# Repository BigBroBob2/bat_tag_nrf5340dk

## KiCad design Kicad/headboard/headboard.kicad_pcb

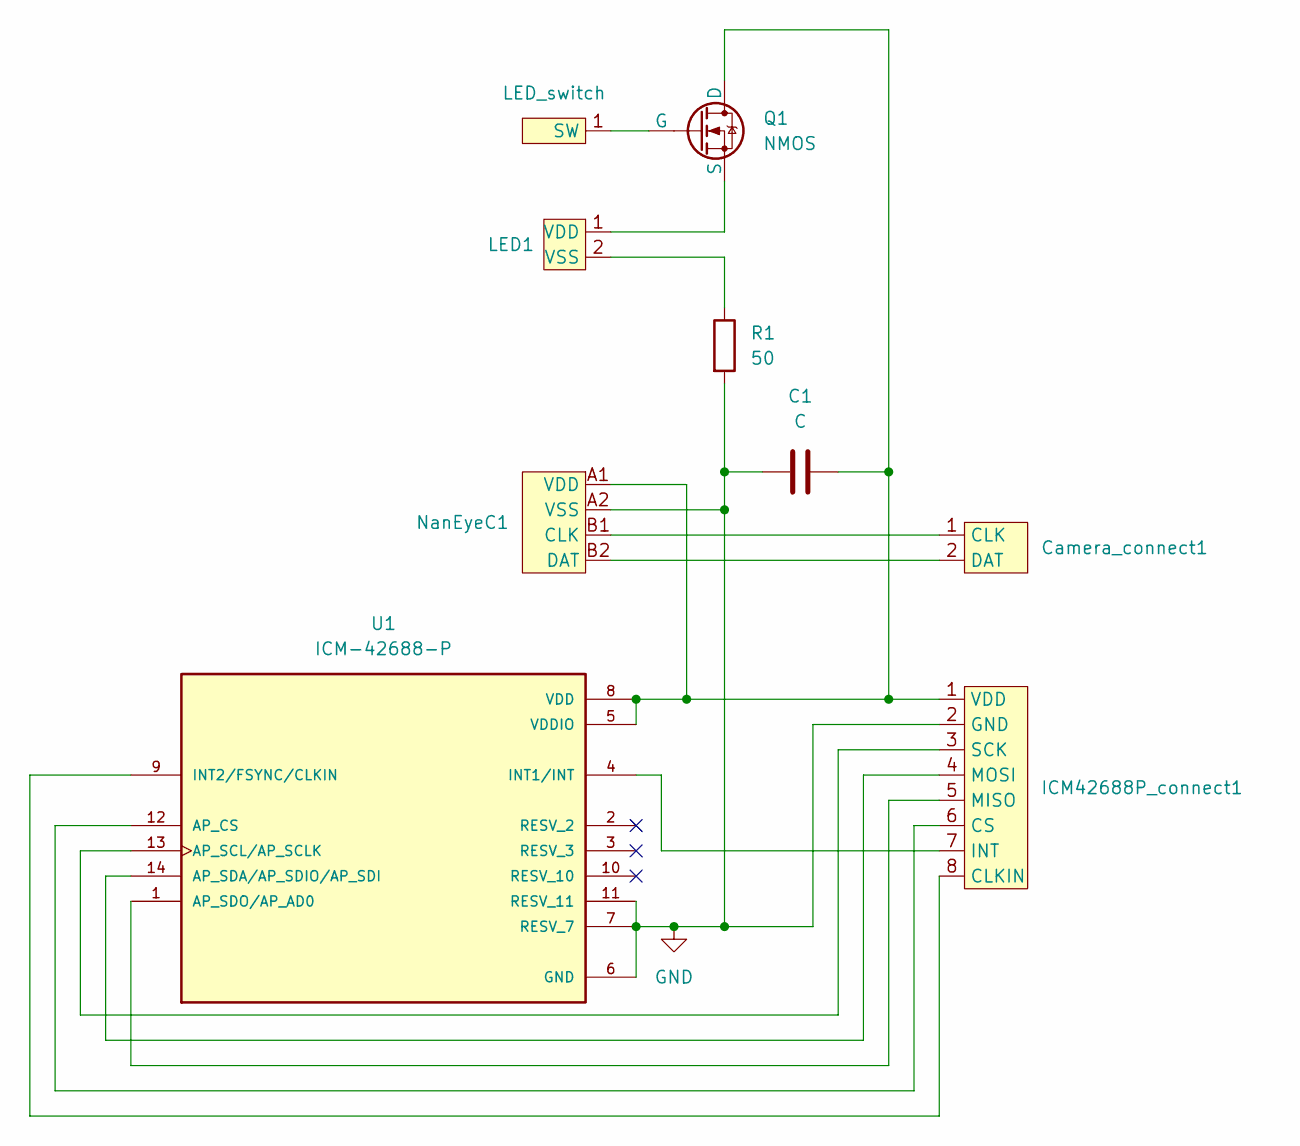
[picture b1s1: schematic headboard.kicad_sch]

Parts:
C1: C; C_0603_1608Metric
Camera_connect1: camera_connect
Camera_connect2: LED_switch
ICM42688P_connect1: ICM42688P_connect
LED1: LED_1206_3216Metric
NanEyeC1: NanEyeC
Q1: NMOS; SOT-23
R1: 50; R_0603_1608Metric
U1: ICM-42688-P; PQFN50P300X250X97-14N; PARTREV 1.2

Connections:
GND: C1.1, ICM42688P_connect1.2 (GND), NanEyeC1.A2 (VSS), R1.2, U1.6 (GND), U1.7 (RESV_7), U1.11 (RESV_11)
unnamed: Camera_connect1.1 (CLK), NanEyeC1.B1 (CLK)
unnamed: Camera_connect1.2 (DAT), NanEyeC1.B2 (DAT)
unnamed: Camera_connect2.1 (SW), Q1.2 (G)
unnamed: ICM42688P_connect1.8 (CLKIN), U1.9 (INT2/FSYNC/CLKIN)
unnamed: ICM42688P_connect1.6 (CS), U1.12 (AP_CS)
unnamed: ICM42688P_connect1.7 (INT), U1.4 (INT1/INT)
unnamed: ICM42688P_connect1.5 (MISO), U1.1 (AP_SDO/AP_AD0)
unnamed: ICM42688P_connect1.4 (MOSI), U1.14 (AP_SDA/AP_SDIO/AP_SDI)
unnamed: ICM42688P_connect1.3 (SCK), U1.13 (AP_SCL/AP_SCLK)
unnamed: C1.2, ICM42688P_connect1.1 (VDD), NanEyeC1.A1 (VDD), Q1.1 (D), U1.5 (VDDIO), U1.8 (VDD)
unnamed: LED1.1 (VDD), Q1.3 (S)
unnamed: LED1.2 (VSS), R1.1

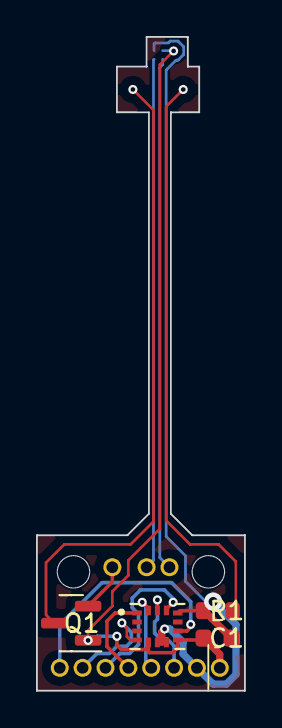
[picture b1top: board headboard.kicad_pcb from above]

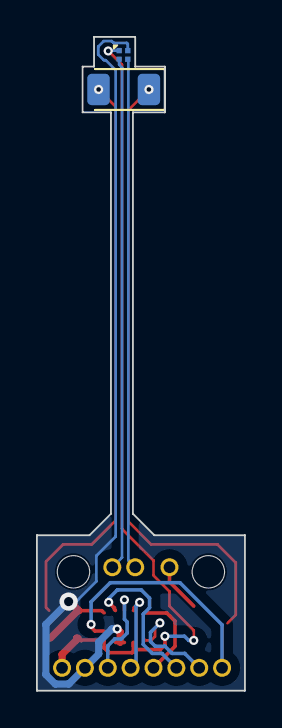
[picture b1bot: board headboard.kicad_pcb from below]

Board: 2 copper layers, 11.6 x 36.3 mm, 9 parts (2 on the bottom side), 13 nets.

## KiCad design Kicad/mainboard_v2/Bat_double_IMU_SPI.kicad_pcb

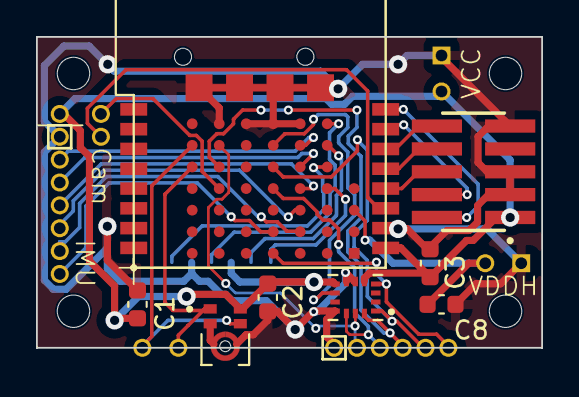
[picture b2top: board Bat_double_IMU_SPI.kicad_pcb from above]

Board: 2 copper layers, 28.1 x 17.3 mm, 15 parts (1 on the bottom side), 28 nets.

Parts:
C1, C2, C3, C8: C; C_0603_1608Metric
Cam: camera_connect
I2S_debug1: I2S_debug
IMU: ICM42688P_connect
J1: FTSH-105-01-F-DV-P-TR; SAMTEC_FTSH-105-01-F-DV-P-TR
J2: MEM2075-00-140-01-A; GCT_MEM2075-00-140-01-A
MK1: SPH0655LM4H-1; MIC_SPH0655LM4H-1
SPI_debug1: SPI_debug
U1: BT40F
U3: ICM-42688-P; PQFN50P300X250X97-14N
VCC: Battery_entry
VDDH: Battery_entry

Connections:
/BodyICM_CLKIN: U1.P$C1 (C1/P031), U3.9 (INT2/FSYNC/CLKIN)
/HeadICM_CLKIN: IMU.8 (CLKIN), U1.P$C5 (C5/P020-TX)
/I2S_SCK_M: I2S_debug1.1, MK1.4 (CLOCK), U1.P$Z1 (Z1/P110)
/I2S_SDIN: I2S_debug1.2, MK1.1 (DATA), U1.P$Z2 (Z2/P111)
/SPI1_CS: IMU.6 (CS), U1.P$D4 (D4/P029)
/SPI1_INT: IMU.7 (INT), U1.P$D5 (D5/P022-RX)
/SPI1_MISO: IMU.5 (MISO), U1.P$D3 (D3/P028)
/SPI1_MOSI: IMU.4 (MOSI), U1.P$D2 (D2/P027)
/SPI1_SCK: IMU.3 (SCK), U1.P$D1 (D1/P026)
/SPI2_CS: SPI_debug1.3, U1.P$C3 (C3/P024), U3.12 (AP_CS)
/SPI2_INT: SPI_debug1.6, U1.P$C6 (C6/P025), U3.4 (INT1/INT)
/SPI2_MISO: SPI_debug1.5, U1.P$C2 (C2/P021-CTS), U3.1 (AP_SDO/AP_AD0)
/SPI2_MOSI: SPI_debug1.4, U1.P$A2 (A2/P007), U3.14 (AP_SDA/AP_SDIO/AP_SDI)
/SPI2_SCK: SPI_debug1.2, U1.P$A1 (A1/P006), U3.13 (AP_SCL/AP_SCLK)
/SPI3_CS: J2.P2 (CD/DAT3), U1.P$E3 (E3/P107)
/SPI3_MISO: J2.P7 (DAT0), U1.P$E2 (E2/P106)
/SPI3_MOSI: J2.P3 (CMD), U1.P$E1 (E1/P105)
/SPI3_SCK: J2.P5 (CLK), U1.P$E0 (E0/P104)
/SPI4_MOSI: Cam.2 (DAT), U1.P$11 (P009/BUTTON)
/SPI4_SCK: Cam.1 (CLK), U1.P$A3 (A3/P008)
/SWD_NC: J1.08, U1.P$13 (P030/LED)
GND: C1.1, C2.1, C3.1, C8.1, IMU.2 (GND), J1.03, J1.05, J1.09, J2.P6 (VSS), J2.SH1 (SHIELD), J2.SH2 (SHIELD), J2.SH3 (SHIELD), J2.SH4 (SHIELD), MK1.2 (SELECT), MK1.3 (GND), SPI_debug1.1, U1.P$10 (GND), U1.P$A0 (A0/VSS1), U1.P$B0 (B0/VSS2), U1.P$C0 (C0/VSS3), U1.P$D0 (D0/VSS4), U1.P$H0 (H0/GND), U1.P$H1 (H1/GND), U1.P$H2 (H2/GND), U1.P$H3 (H3/GND), U3.6 (GND), U3.7 (RESV_7), U3.11 (RESV_11), VCC.2, VDDH.2
unnamed: J1.06, U1.P$12 (P11/SWO)
unnamed: J1.10, U1.P$14 (P21/RESET)
unnamed: J1.04, U1.P$15 (SWCLK)
unnamed: J1.02, U1.P$16 (SWDIO)
VCC: C1.2, C2.2, C3.2, IMU.1 (VDD), J1.01, J2.P4 (VDD), MK1.5 (VDD), U1.P$9 (VDD), U3.5 (VDDIO), U3.8 (VDD), VCC.1
VDDH: C8.2, U1.P$F4 (F4/VDDH), VDDH.1

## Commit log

2023-07-28 init
2023-08-02 write PDM audio into SDcard at 50kHz
2023-08-07 bluetooth is working
2023-08-07 increased bluetooth buf
2023-08-15 i2s interface for pdm mic
2023-08-23 spi interface for ICM42688, interrupt to read mic
2023-08-23 now can sample IMU and mic data together
2023-08-24 now can disable i2s thread and ICM thread
2023-08-28 bluetooth connect to start recording
2023-08-30 Now can record time and IMU buf len
2023-09-01 add 1kHz ICM Interrupt
2023-09-06 Now use ICM_IRQ to sample IMU data
2023-09-11 use circular buffer for IMU recording
2023-09-15 try on ICM internal FIFO, not working donotuse
2023-09-15 i2s semaphore wait forever to 1us, no IRQ gap
2023-09-17 IMU sample data dropout fixed
2023-09-18 Change I2S freq from 2M to 1MHz, no dropout
2023-09-20 Add Kicad project, First version schematic
2023-09-25 Kicad first version layout update
2023-10-03 Kicad PCB update
2023-11-01 BT40 working, I2S LRCK_M and SDIN pins switched
2023-11-01 try sync imu and i2s clk, not working
2023-11-03 Achieve multiple trial recording
2023-11-03 multiple trial update also for BT40
2023-11-10 Remove throw_away_first_i2s_buffer
2023-11-13 update to make code on BT40 and DK same
2023-11-29 Try to add 2nd IMU with I2C, I2C error
2023-11-29 Add 2nd IMU SPI, multi-trial cir-buf out range
2023-12-01 multi-trial cir-buf outrange fixed,need enable SPI
2023-12-01 IMU_data[9], save 6D data and time and idx
2023-12-04 Add second IMU within one SPI bus
2023-12-08 Update code on BT40 for bat demo
2024-01-29 add NanEyeC camera, not tested
2024-02-02 Add camera thread
2024-02-08 thread-time-working version with camera
2024-02-08 20 fps camera with ROI and no threshold
2024-03-08 fixed VDDH high vol mode, improved trial_count when reset
2024-03-11 update bluetooth string command
2024-03-18 add real time camera 4*4 avg downsample
2024-03-20 add different camera zoom_mode
2024-03-21 add timestamp to camera frame and audio block
2024-03-22 add imu and cam enable/disable, and cam_fs bt command
2024-04-01 move camera init inside trial loop, which fixed camera 1st frame
2024-04-03 init camera circular buf read and write index before every trial
2024-04-08 update PCB and code for v2
2024-08-05 upload headboard flex pcb
